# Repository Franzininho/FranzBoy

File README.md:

View this project on [CADLAB.io](https://cadlab.io/project/27016). 

# FranzBoy by Franzininho

FranzBoy é uma placa no formato de game. Possui display OLED, 6 teclas e é baseado no microcontolador Atmega328.

## Pinagem

OLED:
- PC4: SDA - A4
- PC5: SCL - A5
 
BOTÕES:
- UP:	PD3 - D3
- DOWN: PD4 - D4
- LEFT: PD2 - D2
- RIGHT: PD5 - D5
- A: PD6 - D6
- B: PD7 - D7

USB:
- D+: PD2 - D2
- D-: PD4 - D4

BUZZER: PB1 - D9

IR: PB2 - D10
 
LED: PB5 - D13

## upload do código usando bootloader do Arduino UNO e conversor USB/Serial

Como ainda não temos um bootloader específico para a Franzboy, vamos usar o bootloader do Arduino Uno emprestado.

Na IDE do Arduino, configure para a programação da placa Arduino UNO:
- Ferramentas-> placa: Arduino Uno

Selecione também a porta USB atribuida ao conversor USB serial.

Faça a seguinte ligação:

|  FranzBoy | Conversor USB/Serial  |
| ------------ | ------------ |
|  DTR | DTR  |
|  RX | RX  |
|  TX | TX  |
|  VCC | VCC  |
|  CTS |  CTS |
|  GND |  GND |

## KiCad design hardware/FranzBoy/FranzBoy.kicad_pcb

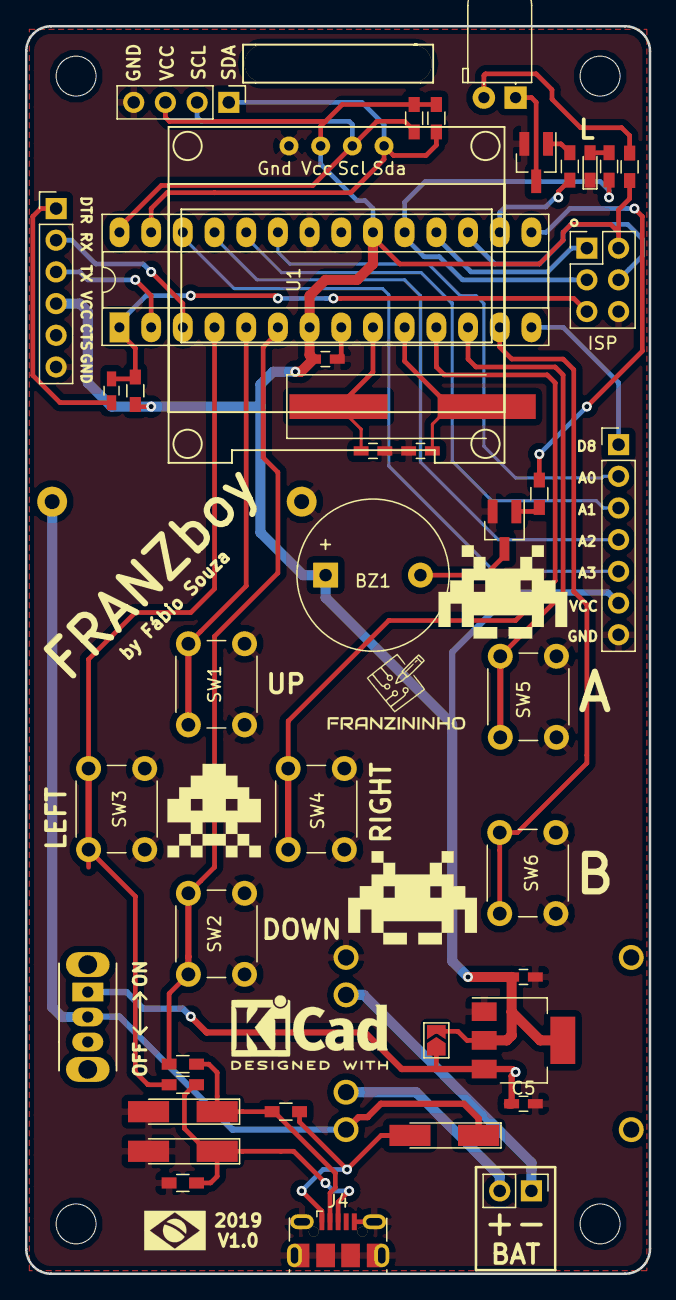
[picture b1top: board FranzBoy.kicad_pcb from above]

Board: 2 copper layers, 50.0 x 100.0 mm, 45 parts (1 on the bottom side), 39 nets.

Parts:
BT1: Battery_Cell; CR2032_HOLDER
BZ1: Buzzer; Buzzer_12x9.5RM7.6
C1, C4: 100nF; C_0603_HandSoldering
C2, C3: 22pF; C_0603_HandSoldering
C5, C6: 10uF; C_0603_HandSoldering
D1: LED; LED_0603_HandSoldering
D2, D3: D_Zener; D_MiniMELF_Handsoldering
D4: 1N4148; D_MiniMELF_Handsoldering
D5: LD271; LED_D5.0mm_Horizontal_O1.27mm_Z3.0mm
ISP: AVR-ISP-6; Pin_Header_Straight_2x03_Pitch2.54mm
J2: Conn_01x06_Male; Pin_Header_Straight_1x06_Pitch2.54mm
J3: Conn_01x02_Male; Pin_Header_Straight_1x02_Pitch2.54mm
J4: USB_B_Micro; USB_Micro-B-LCSC-C10418-and-C40946-C319167
J5: Conn_01x04_Male; Pin_Header_Straight_1x04_Pitch2.54mm
J6: Conn_01x07_Male; Pin_Header_Straight_1x07_Pitch2.54mm
JP1: SolderJumper_2_Open; SolderJumper-2_P1.3mm_Open_TrianglePad1.0x1.5mm
LCD1: Oled96
Q1, Q2: MMBT3904; SOT-23_Handsoldering
R1: 10k; R_0603_HandSoldering
R2, R3: 4k7; R_0603_HandSoldering
R4, R9, R10, R11: 1k; R_0603_HandSoldering
R5: 1k5; R_0603_HandSoldering
R6: 1M; R_0603_HandSoldering
R7, R8: 68R; R_0603_HandSoldering
SW1, SW2, SW3, SW4, SW5, SW6: SW_Push; SW_PUSH_6mm_h4.3mm
SW7: SW_SPDT; SW_HH_SS12D07-G4-2
U1: ATmega328-PU; DIP-28_W7.62mm_Socket_LongPads
U2: LM1117-3.3; SOT-223-3_TabPin2
U3: TP4056_BREAKOUT
Y1: 16 MHz; Crystal_SMD_HC49-SD_HandSoldering

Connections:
+5V: D4.2, J4.1, R5.2
AN0: J6.2, U1.23
AN1: J6.3, U1.24
AN2: J6.4, U1.25
AN3: J6.5, U1.26
BT_A: SW5.1, U1.12
BT_B: SW6.1, U1.13
BT_DOWN: R7.2, SW2.1, U1.6
BT_LEFT: R8.2, SW3.1, U1.4
BT_RIGTH: SW4.1, U1.11
BT_UP: SW1.1, U1.5
BUZZER: R9.2, U1.15
D8: J6.1, U1.14
DTR: C1.1, J2.1
GND: BT1.2, C2.1, C3.1, C4.2, C5.2, C6.2, D1.1, D2.2, D3.2, ISP.6, J2.6, J4.5, J4.6, J5.4, J6.7, LCD1.4, Q1.2, Q2.2, R6.1, SW1.2, SW2.2, SW3.2, SW4.2, SW5.2, SW6.2, U1.8, U1.22, U2.1, U3.6
I2C_SCL: J5.2, LCD1.2, R3.2, U1.28
I2C_SDA: J5.1, LCD1.1, R2.2, U1.27
IR: R10.2, U1.16
MISO: ISP.1, U1.18
MOSI: ISP.4, U1.17
unnamed: BT1.1, D4.1, SW7.2, U3.3
unnamed: BZ1.2, Q1.3
unnamed: C2.2, U1.9, Y1.1
unnamed: C3.2, U1.10, Y1.2
unnamed: C5.1, JP1.1, SW7.1, U2.3
unnamed: D1.2, R4.1
unnamed: D2.1, J4.2, R5.1, R7.1
unnamed: D3.1, J4.3, R6.2, R8.1
unnamed: D5.1, Q2.3
unnamed: D5.2, R11.1
unnamed: J3.1, U3.5
unnamed: J3.2, U3.4
unnamed: Q1.1, R9.1
unnamed: Q2.1, R10.1
RST: C1.2, ISP.5, R1.2, U1.1
RX: J2.2, U1.3
SCK: ISP.3, R4.2, U1.19
TX: J2.3, U1.2
VCC: BZ1.1, C4.1, C6.1, ISP.2, J2.4, J5.3, J6.6, JP1.2, LCD1.3, R1.1, R2.1, R3.1, R11.2, U1.7, U1.20, U2.2

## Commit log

2019-06-05 Editing the README to informations
2019-06-19 Adionado programa exemplo: Space Invaders
2019-06-19 Adionado projeto de hardware
2019-06-19 Adiconada a licença do Hardware: CERN ohl V1_2 ou acima
2019-06-19 Inicio dos trabalhos com VUSB
2019-06-19 pdf do schematico
2019-06-19 update VUSB link
2019-07-05 Doom-nano by David Ruiz
2019-10-16 Ajuste de construção do display OLED
2019-10-18 Adiconado visualizalção para montagem através da ferramenta Interactive HTML BOM
2019-11-01 Atualizadas as informações do Readme
2023-06-06 Backlink to CADLAB.io has been added.
